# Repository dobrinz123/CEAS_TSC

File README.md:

# InkTime v6 — E-Paper Smartwatch

Smartwatch cu ecran e-paper, Bluetooth Low Energy si baterie LiPo reincarcabila prin USB-C.

**Curs:** TSC (Testarea Sistemelor de Calcul), Anul 3  
**Tool:** Fusion 360 Electronics (EAGLE format)  
**Producator:** JLCPCB — 4 straturi, stackup JLC04161H-7628, finish ENIG

---

## Block Diagram

```
                        USB-C (J4)
                           |
                     USBLC6-2SC6Y (D4)
                       ESD Protection
                           |
            +--------------+---------------+
            |                              |
      BQ25180 (IC3)                   nRF52840 (U1)
      LiPo Charger                  BLE5 + ARM M4F
      I2C addr 0x6A                    64MHz MCU
            |                     /    |    |    \
        LiPo Battery         SPI   I2C  GPIO  USB
            |                  |     |    |
      MAX17048 (U1)        E-Paper  Bus  Buttons
      Fuel Gauge           Display  |    (3x SW)
      I2C addr 0x36       1.54"    |
            |              GDEW0154 |
      RT6160 (IC2)              +---+---+---+
      Buck-Boost DC/DC         |   |   |   |
      3.3V Output          BMA421 MAX  BQ  DRV2605
                           IMU  17048 25180 Haptic
                           0x18  0x36 0x6A  0x5A
                                            |
                                        Shaker Motor
                                        LCM1027B3605F
```

---

## Specificatii

| Parametru | Valoare |
|-----------|---------|
| MCU | nRF52840-QIAA (BLE 5.0, ARM Cortex-M4F, 64MHz) |
| Display | GDEW0154M09 1.54" e-paper (200x200px) |
| Baterie | LiPo 250mAh, BQ25180 charger |
| IMU | BMA421 accelerometru + step counter |
| Haptics | DRV2605L + LCM1027B3605F motor ERM |
| Fuel Gauge | MAX17048 LiPo gauge |
| DC/DC | RT6160 buck-boost, 3.3V output |
| USB | USB-C (KH-TYPE-C-16P), USBLC6-2SC6Y ESD |
| Debug | TC2030-IDC TagConnect SWD |
| PCB | 46x35mm, 4 straturi, 1.6mm, ENIG |

---

## Stackup PCB

| Strat | Functie | Cupru |
|-------|---------|-------|
| F.Cu (Top) | Semnal + Componente | 1oz (35um) |
| In1.Cu | Plan GND | 0.5oz (17.5um) |
| In2.Cu | Plan 3V3 | 0.5oz (17.5um) |
| B.Cu (Bottom) | Rutare semnal | 1oz (35um) |

---

## Structura Proiect

```
Hardware/
|-- inktime_v6.sch                # Schematic EAGLE
|-- inktime_v6.brd                # PCB layout (46x35mm, 4 straturi)
Manufacturing/
|-- inktime_v6_gerbers.zip        # Fisiere Gerber pt JLCPCB
|-- inktime_v6_BOM_jlcpcb.csv    # Bill of Materials (part numbers LCSC)
|-- inktime_v6_CPL_jlcpcb.csv    # Pick-and-Place (coordonate componente)
Mechanical/
|-- inktime_v6_cas.f3d            # Model 3D Fusion 360 (carcasa + componente)
|-- inktime_v6.step               # Export STEP
Images/
|-- Baterie.png                   # Model 3D baterie LiPo
|-- Carcasa_ceas.png              # Randare carcasa (vedere 1)
|-- Carcasa_ceas_2.png            # Randare carcasa (vedere 2)
|-- Ecran_e_paper.png             # Model 3D ecran e-paper
|-- Model_PCB.png                 # Model 3D PCB cu componente
|-- Motor.png                     # Model 3D motor vibratii
|-- Randare_PCB.png               # Randare PCB complet
LICENSE
README.md
```

---

## Note Fabricatie

- **Producator**: JLCPCB 4 straturi, stackup JLC04161H-7628
- **Finish**: ENIG (Electroless Nickel Immersion Gold)
- **Grosime PCB**: 1.6mm
- **Cupru**: 1oz exterior, 0.5oz interior
- **Componente**: Toate pe stratul TOP, asamblare SMT
- **Montare manuala**: retea matching RF, test pads, conector FPC (J1), TagConnect (J3), motor vibratii

---

## Autor

Dobrin David — TSC (Testarea Sistemelor de Calcul), 2026

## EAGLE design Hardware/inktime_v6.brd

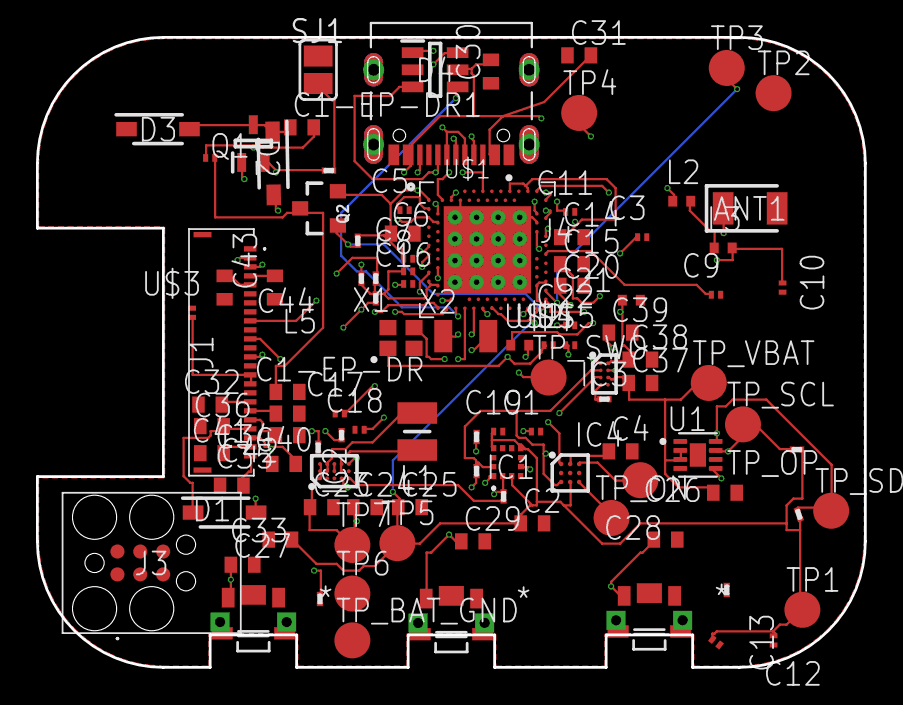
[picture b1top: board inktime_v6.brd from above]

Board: 4 copper layers, 46.0 x 35.0 mm, 105 parts (0 on the bottom side), 70 nets.

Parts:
ANT1: 2450AT18B100E_2450AT18B100E; 2450AT18B100E_ANTC3216X140N
C1, C3: 1pF; NORDIC_NRF_3_RESC0201_L
C1-EP-DR, C24, C39: 10uF; ESP32_C6_LIBRARY_1_ESP32_WROVER_EAGLE-LTSPICE_C0402
C1-EP-DR1: 4.7uF/25V; ESP32_C6_LIBRARY_1_ESP32_WROVER_EAGLE-LTSPICE_C0402
C2, C23, C26, C31: 0.1uF; ESP32_C6_LIBRARY_1_ESP32_WROVER_EAGLE-LTSPICE_C0402
C4, C27, C28, C29, C37, C38: 1uF; ESP32_C6_LIBRARY_1_ESP32_WROVER_EAGLE-LTSPICE_C0402
C5, C7, C8, C12, C19: 100nF; NORDIC_NRF_3_RESC0201_L
C6, C14, C20: 4.7µF; ESP32_C6_LIBRARY_1_ESP32_WROVER_EAGLE-LTSPICE_C0402
C9: 820pF; NORDIC_NRF_3_RESC0201_L
C10, C13, C22: N.C.; NORDIC_NRF_3_RESC0201_L
C11: 100pF; NORDIC_NRF_3_RESC0201_L
C15: 1.0µF; ESP32_C6_LIBRARY_1_ESP32_WROVER_EAGLE-LTSPICE_C0402
C16: 47nF; NORDIC_NRF_3_RESC0201_L
C17, C18: 12pF; NORDIC_NRF_3_RESC0201_L
C21: 4.7µF; NORDIC_NRF_3_RESC0402_L
C25, C33: 22uF; ESP32_C6_LIBRARY_1_ESP32_WROVER_EAGLE-LTSPICE_C0402
C30: 4.7uF; ESP32_C6_LIBRARY_1_ESP32_WROVER_EAGLE-LTSPICE_C0402
C32, C34, C35, C36, C40, C41, C42, C43, C44: 1uF/50V; ESP32_C6_LIBRARY_1_ESP32_WROVER_EAGLE-LTSPICE_C0402
D1, D2, D3: ESP32_C6_LIBRARY_5_MBR0530; ESP32_C6_LIBRARY_5_SOD3716X135N
D4: ESP32_C6_LIBRARY_3_USBLC6-2SC6Y; ESP32_C6_LIBRARY_3_SOT95P280X145-6N
IC1: BMA423_BMA423
IC2: RT6160AWSC_RT6160AWSC; RT6160AWSC_BGA15C40P3X5_140X230X60
IC3: BQ25180YBGR_BQ25180YBGR; BQ25180YBGR_BGA8C40P2X4_100X155X50
IC4: DRV2605YZFR_DRV2605YZFR; DRV2605YZFR_BGA9C50P3X3_144X144X62
J1: 503480-2400_503480-2400; 503480-2400_5034802400
J3: TC2030-IDC_TC2030-IDC; TC2030-IDC_TC2030IDC
J4: KH-TYPE-C-16P_KH-TYPE-C-16P; KH-TYPE-C-16P_KINGHELM_KH-TYPE-C-16P
L1: MLP2016SR47MT0S1_FTC252012SR47MBCA; MLP2016SR47MT0S1_INDC2016X100N
L2, L3: 10µH; NORDIC_NRF_2_RESC0402_L
L5: 68uH; NORDIC_NRF_2_RESC0201_L
Q1: ESP32_C6_LIBRARY_6_SI1308EDL-T1-GE3; ESP32_C6_LIBRARY_6_SOT65P210X110-3N
Q2: 20V/4.2A/52mΩ/1.4W; ESP32_C6_LIBRARY_4_ESP32_C6_LIBRARY_4_ESP32_C6_LIBRARY_4_ES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
R1, R2, R3: 0; CPF0201D7K68C1_0201
R4, R5: 3K3; CPF0201D7K68C1_0201
R6: 0.47; CPF0201D7K68C1_0201
R7: 2.2; CPF0201D7K68C1_0201
R8, R9, R10, R11, R12, R13, R14, R16: 10K; CPF0201D7K68C1_0201
SJ1: 0; ESP32_C6_LIBRARY_7_JUMPER_SJ
SW1, SW2, SW3: 2025-10-22_07-23-44_LIBRARY_EVP-AKE31ASW_EVP-AKE3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; 2025-10-22_07-23-44_LIBRARY_SW_EVP-AKE31A_PAN
TP1, TP2, TP3, TP4, TP5, TP6, TP7: HECTOR_WATCH_1_TPTP20R; HECTOR_WATCH_1_TP20R
TP_BAT_GND: HECTOR_WATCH_1_TPTP20R; HECTOR_WATCH_1_TP20R
TP_ON: HECTOR_WATCH_1_TPTP20R; HECTOR_WATCH_1_TP20R
TP_OP: HECTOR_WATCH_1_TPTP20R; HECTOR_WATCH_1_TP20R
TP_SCL: HECTOR_WATCH_1_TPTP20R; HECTOR_WATCH_1_TP20R
TP_SDA: HECTOR_WATCH_1_TPTP20R; HECTOR_WATCH_1_TP20R
TP_SWO: HECTOR_WATCH_1_TPTP20R; HECTOR_WATCH_1_TP20R
TP_VBAT: HECTOR_WATCH_1_TPTP20R; HECTOR_WATCH_1_TP20R
U1: ESP32_C6_LIBRARY_MAX17048G+T10; ESP32_C6_LIBRARY_SON50P200X200X80-9N
U$1: NORDIC_NRF_4_NRF52840_QF; NORDIC_NRF_4_AQFN50P700X700X85_HS-74N
U$2: 3.9nH; NORDIC_NRF_2_RESC0402_L
U$3: 1uF/50V; NORDIC_NRF_3_RESC0201_L
U$4, U$5: 12pF; NORDIC_NRF_3_RESC0201_L
X1: 32MHz; NORDIC_NRF_BT-XTAL_2016_N
X2: 32.768kHz; NORDIC_NRF_1_XTAL_3215_N

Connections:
3V3: C2.1, C6.1, C7.1, C8.1, C12.1, C13.1, C14.1, C19.1, C25.1, C33.1, IC1.3, IC1.7, IC1.10, IC2.E3, IC4.C2, Q2.2, R4.1, R5.1, R10.2, R11.2, R12.2, R16.2, TP1.TP, TP5.TP, U$1.P$A18, U$1.P$A22, U$1.P$AD14, U$1.P$AD23, U$1.P$B1, U$1.P$W1, U$1.P$Y2
ALERT: U1.5, U$1.P$J24
D+: D4.4, U$1.P$AD6
D-: D4.6, U$1.P$AD4
DEC3: C11.1, U$1.P$D23
DEC4_6: C10.1, C15.1, C16.1, L3.2, U$1.P$B5, U$1.P$E24
DN: D4.1, J4.A7, J4.B7
DP: D4.3, J4.A6, J4.B6
EPD: J1.15, J1.16, U$3.2
EPD_3V3: C1-EP-DR.1, L5.1, Q2.3
EPD_BUSY: J1.9, U$1.P$AD12
EPD_CS: J1.12, U$1.P$K2
EPD_DC: J1.11, U$1.P$AD10
EPD_RST: J1.10, U$1.P$AC11
GDR: J1.2, Q1.1, R8.2
GND: C1.2, C1-EP-DR.2, C2.2, C3.2, C4.2, C5.2, C6.2, C7.2, C8.2, C9.2, C10.2, C11.2, C12.2, C13.2, C14.2, C15.2, C16.2, C17.1, C18.1, C19.2, C20.2, C21.2, C22.2, C23.2, C24.2, C25.2, C26.2, C27.2, C28.2, C29.2, C30.1, C31.1, C32.1, C33.2, C34.1, C35.1, C36.1, C37.2, C38.2, C39.2, C40.1, C41.1, C43.1, C44.1, D3.1, D4.2, IC1.8, IC1.9, IC2.B1, IC2.C1, IC2.C2, IC2.C3, IC3.D2, IC4.B1, IC4.B3, J1.8, J1.17, J1.MP1, J1.MP2, J4.A1_B12, J4.A12_B1, J4.SH1, J4.SH2, J4.SH3, J4.SH4, R3.1, R7.1, R8.1, R9.1, R13.1, R14.2, SJ1.1, SW1.1, SW2.1, SW3.1, TP6.TP, TP_BAT_GND.TP, U1.1, U1.4, U1.6, U1.9, U$1.P$74, U$1.P$75, U$1.P$76, U$1.P$77, U$1.P$78, U$1.P$79, U$1.P$80, U$1.P$81, U$1.P$82, U$1.P$83, U$1.P$84, U$1.P$85, U$1.P$86, U$1.P$87, U$1.P$88, U$1.P$89, U$1.P$90, U$1.P$B7, U$1.P$F23, U$3.1, U$4.2, U$5.2, X1.2, X1.4
GND3: IC1.1, R3.2
HAPTIC_EN: IC4.A1, U$1.P$U1
IMU_INT1: IC1.5, U$1.P$N1
IMU_INT2: IC1.6, U$1.P$P2
LX1: IC2.B2, IC2.B3, L1.1
LX2: IC2.D2, IC2.D3, L1.2
MOSI: J1.14, U$1.P$B13
unnamed: C5.1, U$1.P$C1
unnamed: C20.1, U$1.P$AC5
unnamed: ANT1.1, C1.1, C22.1, U$2.2
unnamed: C3.1, U$1.P$H23, U$2.1
unnamed: L2.2, L3.1
unnamed: U$1.P$A23, U$5.1, X1.3
unnamed: IC2.D1, R2.2
unnamed: C1-EP-DR1.2, D1.2, L5.2
unnamed: IC2.E1, R1.2
unnamed: C1-EP-DR1.1, D2.1, D3.2, Q1.3
unnamed: C9.1, U$1.P$N24
unnamed: IC3.D1, R9.2
unnamed: U$1.P$B24, U$4.1, X1.1
unnamed: R6.1, SJ1.2
unnamed: L2.1, U$1.P$B3
unnamed: C4.1, IC4.A2
unnamed: J4.A5, R13.2
unnamed: J4.B5, R14.1
unnamed: C43.2, J1.4
unnamed: C44.2, J1.5
unnamed: C32.2, J1.18
unnamed: C34.2, J1.19
unnamed: C35.2, J1.20
unnamed: C41.2, J1.23
unnamed: C42.2, J1.24
OUT+: IC4.A3, TP_OP.TP
OUT-: IC4.C3, TP_ON.TP
P0.00/XL1: C17.2, U$1.P$D2, X2.1
P0.00/XL2: C18.2, U$1.P$F2, X2.2
P0.13: C27.1, R10.1, SW1.2, U$1.P$AD8
P0.14: C28.1, R11.1, SW2.2, U$1.P$AC9
P1.01: Q2.1, R16.1, U$1.P$W24, U$1.P$Y23
P1.02: C29.1, R12.1, SW3.2
PMIC_INT: IC3.A1, U$1.P$T2
PREVGH: C36.2, D1.1, J1.21
PREVGL: C40.2, D2.2, J1.22
RESE: J1.3, Q1.2, R6.2
RESET: TP2.TP, U$1.P$AC13
SCK: J1.13, U$1.P$A12
SCL: IC1.12, IC3.B1, IC4.C1, R2.1, R4.2, TP_SCL.TP, U1.7, U$1.P$M2
SDA: IC1.2, IC3.C1, IC4.B2, R1.1, R5.2, TP_SDA.TP, U1.8, U$1.P$L1
SWDCLK: TP3.TP, U$1.P$AA24
SWDIO: TP4.TP, U$1.P$AC24
SWO: TP_SWO.TP, U$1.P$AD22
VBAT: C26.1, C37.1, IC3.C2, TP_VBAT.TP, U1.2, U1.3
VBUS: C21.1, C30.2, C31.2, C38.1, D4.5, IC3.A2, J4.A4_B9, J4.A9_B4, U$1.P$AD2
VREG: C23.1, C24.1, C39.1, IC2.A1, IC2.A2, IC2.A3, IC3.B2, TP7.TP

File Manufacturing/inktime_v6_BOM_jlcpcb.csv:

Comment,Designator,Footprint,LCSC Part #
0,"R1,R2,R3",0201,C17168
0,SJ1,SJ,C17168
0.1uF,"C2,C23,C26,C31",0402,C14663
0.47,R6,0201,
1.0uF,C15,0402,C15849
100nF,"C12,C19,C5,C7,C8",0201,C14663
100pF,C11,0201,C14858
10K,"R10,R11,R12,R13,R14,R16,R8,R9",0201,C25744
10uF,"C1-EP-DR,C24,C39",0402,C15712
10uH,"L2,L3",0402,C408494
12pF,"C17,C18,U$4,U$5",0201,C30379
1pF,"C1,C3",0201,
1uF,"C27,C28,C29,C37,C38,C4",0402,C15849
1uF/50V,U$3,0201,C15849
1uF/50V,"C32,C34,C35,C36,C40,C41,C42,C43,C44",0402,C15849
2.2,R7,0201,C25879
2025-10-22_07-23-44_LIBRARY_EVP-AKE31ASW_EVP-AKE31A_PAN,"SW1,SW2,SW3",SW-SMD-3x4,
20V/4.2A/52mohm/1.4W,Q2,SOT23-3,
22uF,"C25,C33",0402,C59461
2450AT18B100E_2450AT18B100E,ANT1,0402,C89965
3.9nH,U$2,0402,C95912
32.768kHz,X2,SMD3215,C32346
32MHz,X1,SMD3215,C9001582
3K3,"R4,R5",0201,C25890
4.7uF,"C14,C20,C21,C30,C6",0402,
4.7uF/25V,C1-EP-DR1,0402,
47nF,C16,0201,C14663
503480-2400_503480-2400,J1,FPC-24,
68uH,L5,0201,C132330
820pF,C9,0201,C14858
BMA423_BMA423,IC1,LGA-12,C5242966
BQ25180YBGR_BQ25180YBGR,IC3,DSBGA-8,C2681936
DRV2605YZFR_DRV2605YZFR,IC4,DSBGA-12,C2682232
ESP32_C6_LIBRARY_3_USBLC6-2SC6Y,D4,SOT-363,C7519
ESP32_C6_LIBRARY_5_MBR0530,"D1,D2,D3",SOD-123,C242214
ESP32_C6_LIBRARY_6_SI1308EDL-T1-GE3,Q1,SOT-523,C145065
ESP32_C6_LIBRARY_MAX17048G+T10,U1,DFN8-2x2,C2682616
KH-TYPE-C-16P_KH-TYPE-C-16P,J4,USB-C-16P,C165948
MLP2016SR47MT0S1_FTC252012SR47MBCA,L1,0402,
N.C.,"C10,C13,C22",0201,
NORDIC_NRF_4_NRF52840_QF,U$1,QFN-73,C190794
RT6160AWSC_RT6160AWSC,IC2,WLCSP-15,C7065276
TC2030-IDC_TC2030-IDC,J3,TC2030,

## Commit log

2026-04-10 InkTime v6 - E-Paper Smartwatch Design
2026-04-10 Update BOM and CPL from final PCB

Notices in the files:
parts and their libraries:
COPYRIGHT: Copyright (C) 2025 Ultra Librarian. All rights reserved.
